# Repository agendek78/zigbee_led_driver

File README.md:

# Zigbee 3.0 4-channel LED strip controller

Zigbee 3.0 4-channel LED strip controller. Project includes both firmware and hardware.

## Hardware

The hardware of this device is based on Silicon Labs MGM210L module, commonly used in many Zigbee 3.0 products.

The main features:
- support for 12V/24V LEDs
- individual channel dimming
- support for 2 most common buck converters (for generating 3.3V)
- dual option for switching MOSFETs: for low current (<3A) SOT-23 and high current (<12A) DFN3x3A
- single button for pairing/resetting the device
- single status LED

## Firmware

The firmware is based on the latest Gecko SDK v7.2. The communication protocol used is Zigbee 3.0 (but it can be easily extended to support BLE in the same time, as Silicon Labs offers multi-protocol option).

Firmware features:
- Zigbee 3.0
- auto detection of number of mounted channels (when CH1 is mounted only then single Zigbee endpoint will be reported)
- works with motion sensors (like IKEA or Philips HUE) and remotes that implements OnOff/Level client clusters
- works with centralized (like IKEA Dirigera) and distributed (in ex. HUE) security networks
- doesn't support TouchLink, as this requires manufacturers TL keys
- support Find&Bind for linking with other Zigbee 3.0 devices on gateway-less setup
- each channel can be controlled individually (in ex. CH1 from motion sensor but CH2 from remote)

Following picture shows server clusters view for single channel components mounted (4 channel will have additional endpoints 2,3 and 4).

### Zigbee application operation

After boot-up app checks each channel output for mounted transistor, by pulling up channel GPIO and sensing logic level. When transistor is mounted then logic is LOW due to gate capacitance, else is HIGH. When channels are initialized, application checks if device is in network. If is in the network then just starts else executes network steering procedure to find network to join. When no open network is found, device forms it's own distributed security network.

### Button functionality

- long press (>3s) will trigger device factory reset (leave the current network, erase OTA storage and binding table)
- short press will open the network and make first channel identifying (connected LED strip will blink)
- second short press will move to identify next channel. If no more channels then will close the network.

When channel is identifying, other Zigbee 3.0 device can be linked to that channel. Just execute factory reset on other device and it should join the controller network and bind (using Find&Bind) if supported. I was testing this with IKEA devices (various remotes and motion sensors).

To join a remote to multiple channels you have to create zigbee group that includes those channels and bind to that group (unfortunately this requires to send some commands from Silabs CLI, unless you implement this as additional mode for button).

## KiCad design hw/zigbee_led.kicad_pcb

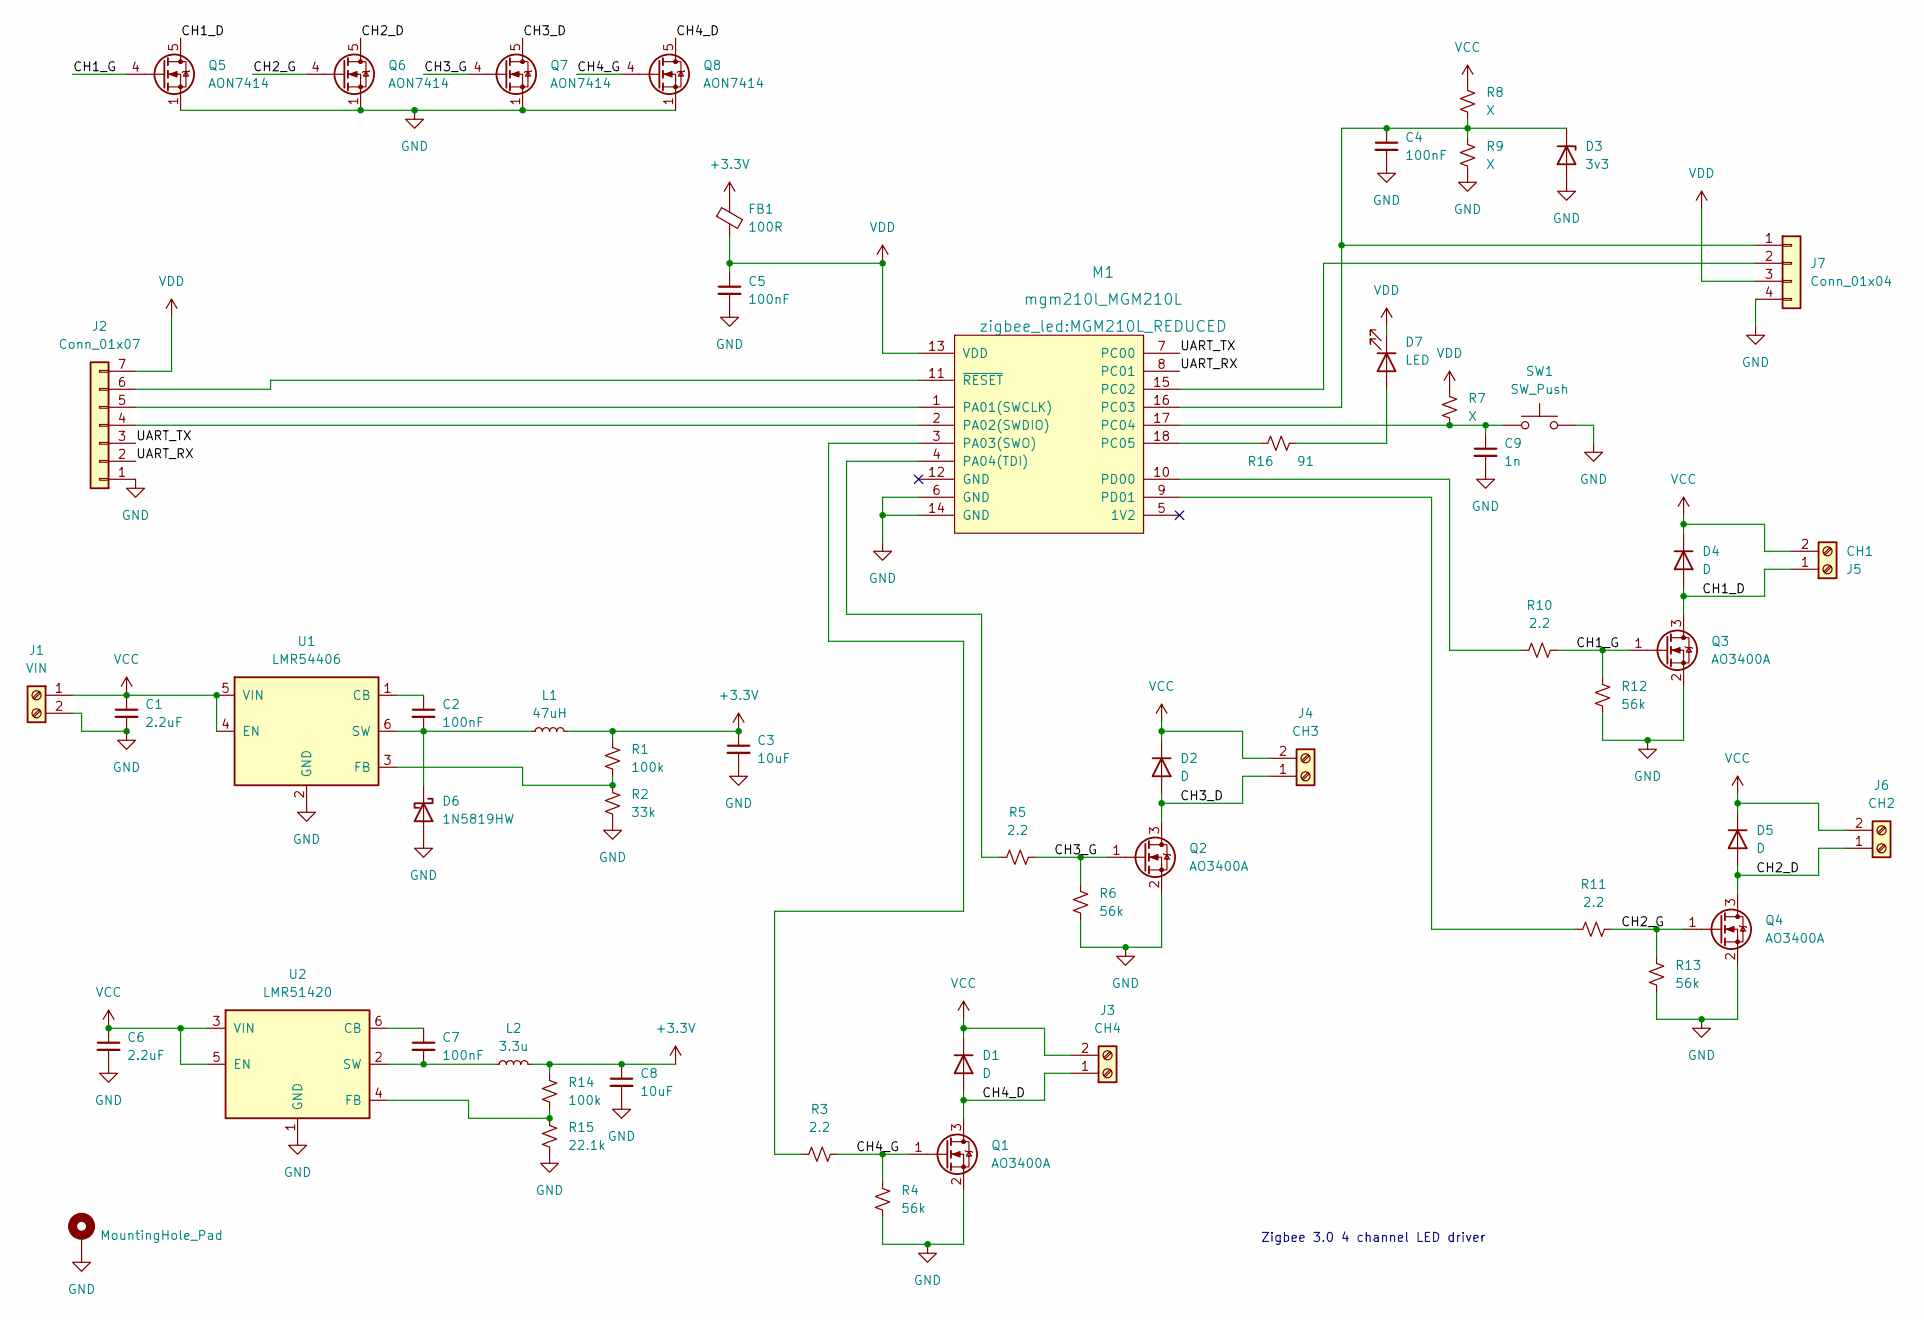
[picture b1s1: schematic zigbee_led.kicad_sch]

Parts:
C1, C6: 2.2uF; C_0603_1608Metric
C2, C7: 100nF; C_0603_1608Metric
C3, C8: 10uF; C_0805_2012Metric
C4, C5: 100nF; C_0402_1005Metric
C9: 1n; C_0402_1005Metric
D1, D2, D4, D5: D; D_MiniMELF
D3: 3v3; D_MiniMELF
D6: 1N5819HW; D_SOD-123
D7: LED; D_0603_1608Metric
FB1: 100R; C_0603_1608Metric
H1: MountingHole_Pad; MountingHole_3.2mm_M3_DIN965_Pad_TopBottom
J1: VIN; TerminalBlock_Phoenix_PT-1,5-2-3.5-H_1x02_P3.50mm_Horizontal
J2: Conn_01x07; PinHeader_1x07_P2.54mm_Vertical
J3: CH4; TerminalBlock_Phoenix_PT-1,5-2-3.5-H_1x02_P3.50mm_Horizontal
J4: CH3; TerminalBlock_Phoenix_PT-1,5-2-3.5-H_1x02_P3.50mm_Horizontal
J5: CH1; TerminalBlock_Phoenix_PT-1,5-2-3.5-H_1x02_P3.50mm_Horizontal
J6: CH2; TerminalBlock_Phoenix_PT-1,5-2-3.5-H_1x02_P3.50mm_Horizontal
J7: Conn_01x04; PinHeader_1x04_P2.54mm_Vertical
L1: 47uH; L_Taiyo-Yuden_MD-4040
L2: 3.3u; L_Taiyo-Yuden_MD-4040
M1: mgm210l_MGM210L; MGM210L_REDUCED
Q1, Q2, Q3, Q4: AO3400A; SOT-23
Q5, Q6, Q7, Q8: AON7414; dual_mos
R1, R14: 100k; R_0402_1005Metric
R2: 33k; R_0402_1005Metric
R3, R5, R10, R11: 2.2; R_0402_1005Metric
R4, R6, R12, R13: 56k; R_0402_1005Metric
R7, R8, R9: X; R_0402_1005Metric
R15: 22.1k; R_0402_1005Metric
R16: 91; R_0603_1608Metric
SW1: SW_Push; SW_SPST_CK_RS282G05A3
U1: LMR54406; SOT-23-6
U2: LMR51420; SOT-23-6

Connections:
+3V3: C3.1, C8.1, FB1.1, L1.2, L2.2, R1.1, R14.1
/CH1_D: D4.2 (A), J5.1, Q3.3 (D), Q5.5 (D)
/CH1_G: Q3.1 (G), Q5.4 (G), R10.2, R12.1
/CH2_D: D5.2 (A), J6.1, Q4.3 (D), Q6.5 (D)
/CH2_G: Q4.1 (G), Q6.4 (G), R11.2, R13.1
/CH3_D: D2.2 (A), J4.1, Q2.3 (D), Q7.5 (D)
/CH3_G: Q2.1 (G), Q7.4 (G), R5.2, R6.1
/CH4_D: D1.2 (A), J3.1, Q1.3 (D), Q8.5 (D)
/CH4_G: Q1.1 (G), Q8.4 (G), R3.2, R4.1
/UART_RX: J2.2, M1.8 (PC01)
/UART_TX: J2.3, M1.7 (PC00)
GND: C1.2, C3.2, C4.2, C5.2, C6.2, C8.2, C9.2, D3.2 (A), D6.2 (A), H1.1, J1.2, J2.1, J7.4, M1.6 (GND), M1.14 (GND), Q1.2 (S), Q2.2 (S), Q3.2 (S), Q4.2 (S), Q5.1 (S), Q5.2 (S), Q5.3 (S), Q6.1 (S), Q6.2 (S), Q6.3 (S), Q7.1 (S), Q7.2 (S), Q7.3 (S), Q8.1 (S), Q8.2 (S), Q8.3 (S), R2.2, R4.2, R6.2, R9.2, R12.2, R13.2, R15.2, SW1.2, U1.2 (GND), U2.1 (GND)
unnamed: C2.1, U1.1 (CB)
unnamed: C2.2, D6.1 (K), L1.1, U1.6 (SW)
unnamed: C4.1, D3.1 (K), J7.1, M1.16 (PC03), R8.2, R9.1
unnamed: C7.1, U2.6 (CB)
unnamed: C7.2, L2.1, U2.2 (SW)
unnamed: C9.1, M1.17 (PC04), R7.2, SW1.1
unnamed: D7.2 (A), R16.2
unnamed: J2.4, M1.2 (PA02(SWDIO))
unnamed: J2.5, M1.1 (PA01(SWCLK))
unnamed: J2.6, M1.11 (~RESET)
unnamed: J7.2, M1.15 (PC02)
unnamed: M1.3 (PA03(SWO)), R3.1
unnamed: M1.4 (PA04(TDI)), R5.1
unnamed: M1.9 (PD01), R11.1
unnamed: M1.10 (PD00), R10.1
unnamed: M1.18 (PC05), R16.1
unnamed: R1.2, R2.1, U1.3 (FB)
unnamed: R14.2, R15.1, U2.4 (FB)
VCC: C1.1, C6.1, D1.1 (K), D2.1 (K), D4.1 (K), D5.1 (K), J1.1, J3.2, J4.2, J5.2, J6.2, R8.1, U1.4 (EN), U1.5 (VIN), U2.3 (VIN), U2.5 (EN)
VDD: C5.1, D7.1 (K), FB1.2, J2.7, J7.3, M1.13 (VDD), R7.1

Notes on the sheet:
Zigbee 3.0 4 channel LED driver

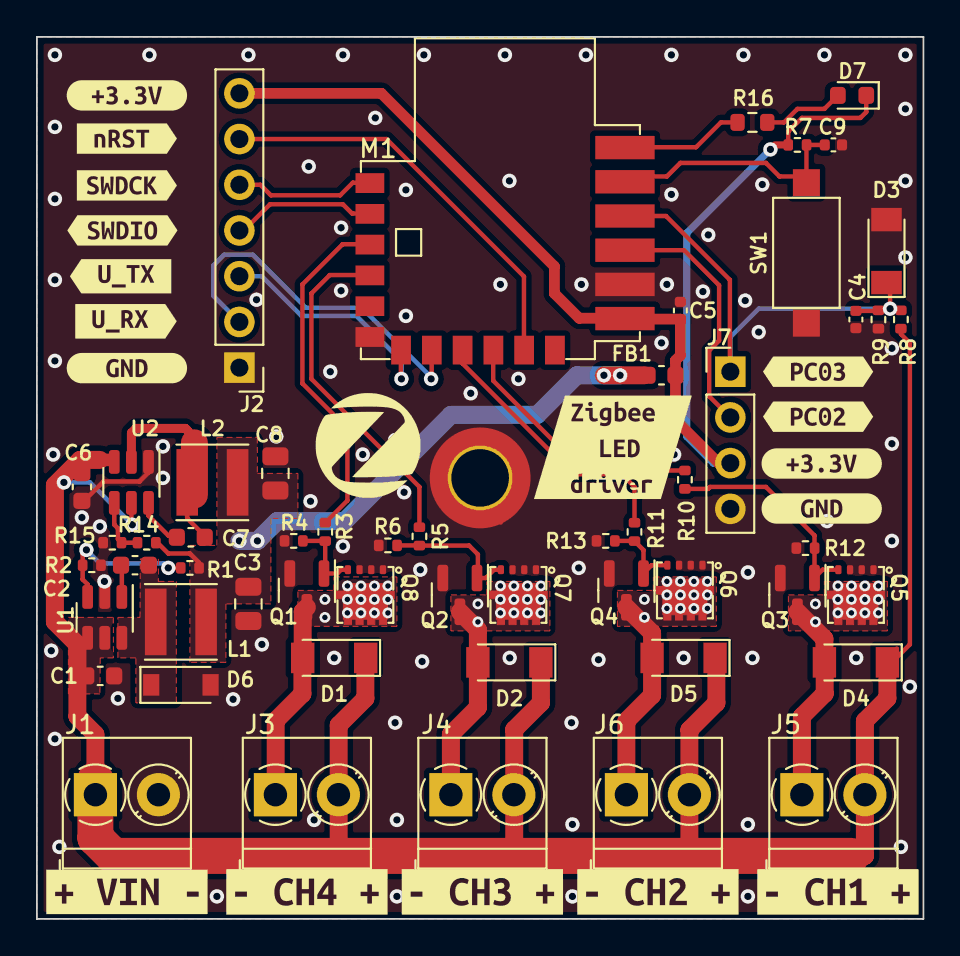
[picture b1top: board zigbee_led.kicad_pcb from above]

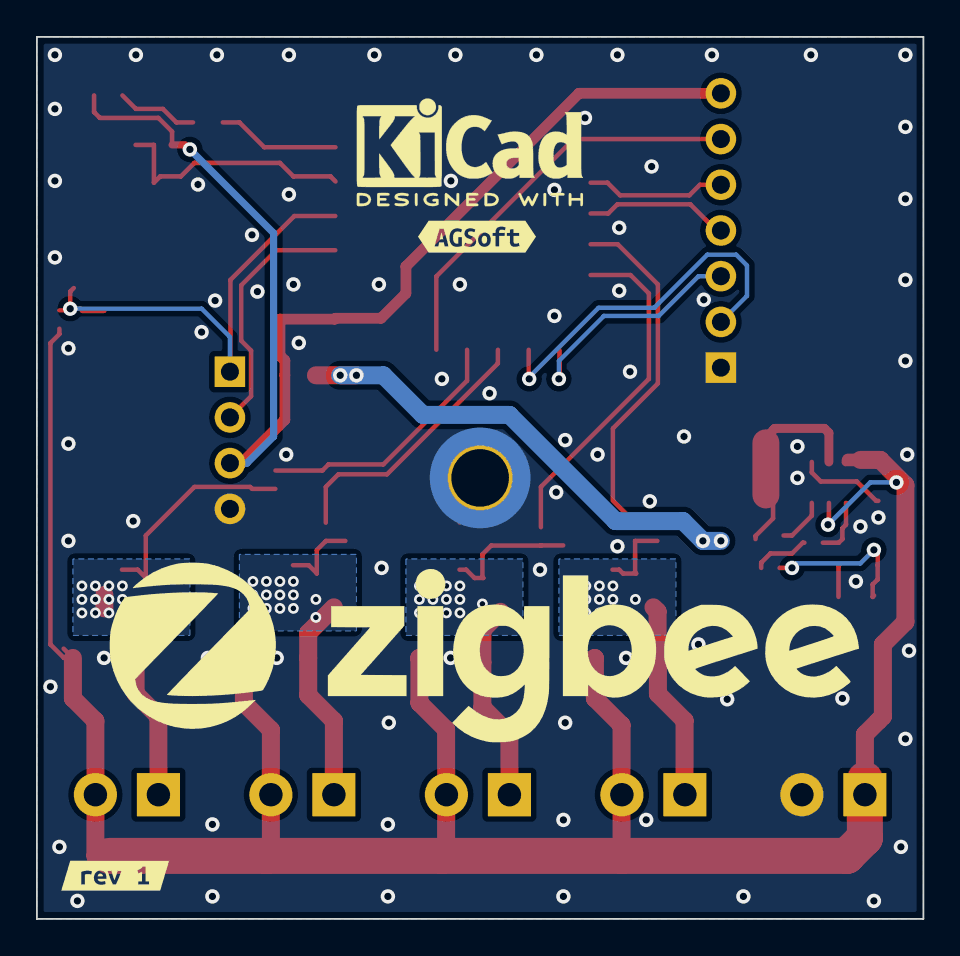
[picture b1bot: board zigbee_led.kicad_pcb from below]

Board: 2 copper layers, 49.2 x 49.0 mm, 74 parts (2 on the bottom side), 32 nets.

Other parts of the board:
kibuzzard-62FBDFF0: G***; kibuzzard-62FBDFF0
kibuzzard-62FBE01C: G***; kibuzzard-62FBE01C
kibuzzard-62FBE02B: G***; kibuzzard-62FBE02B
kibuzzard-62FBE006: G***; kibuzzard-62FBE006
kibuzzard-62FBE011: G***; kibuzzard-62FBE011
kibuzzard-635D774E: G***; kibuzzard-635D774E
kibuzzard-635D775C: G***; kibuzzard-635D775C
kibuzzard-6301F9AD, kibuzzard-6301F9AD#2: G***; kibuzzard-6301F9AD
kibuzzard-6301F96E: G***; kibuzzard-6301F96E
kibuzzard-6301F99C: G***; kibuzzard-6301F99C
kibuzzard-6301F961: G***; kibuzzard-6301F961
kibuzzard-6301F990: G***; kibuzzard-6301F990
kibuzzard-6301FC13: G***; kibuzzard-6301FC13
kibuzzard-6301FC25, kibuzzard-6301FC25#2: G***; kibuzzard-6301FC25
kibuzzard-63020F3A: G***; kibuzzard-63020F3A
kibuzzard-63020FF5: G***; kibuzzard-63020FF5
kibuzzard-63611416: G***; kibuzzard-63611416

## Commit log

2023-05-14 Add hardware KiCAD project
2023-05-14 Initial source code import
2023-05-15 Add project description
2023-12-31 Refactor LEVEL cluster code
    - disable Silabs Level server cluster implementation
    and replace it with own
    - fix restoring default attribute values on factory reset
    - add 'Release' configuration
